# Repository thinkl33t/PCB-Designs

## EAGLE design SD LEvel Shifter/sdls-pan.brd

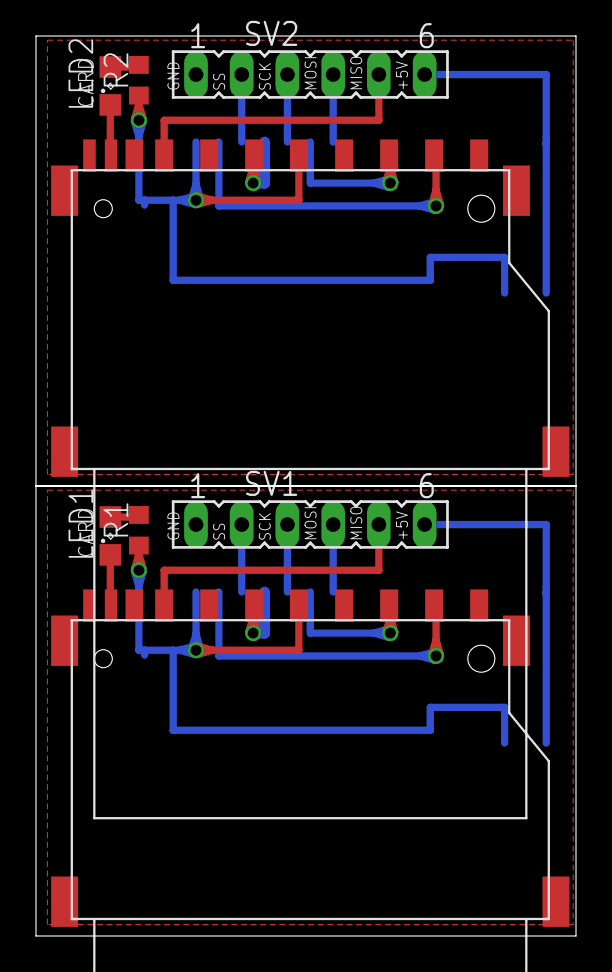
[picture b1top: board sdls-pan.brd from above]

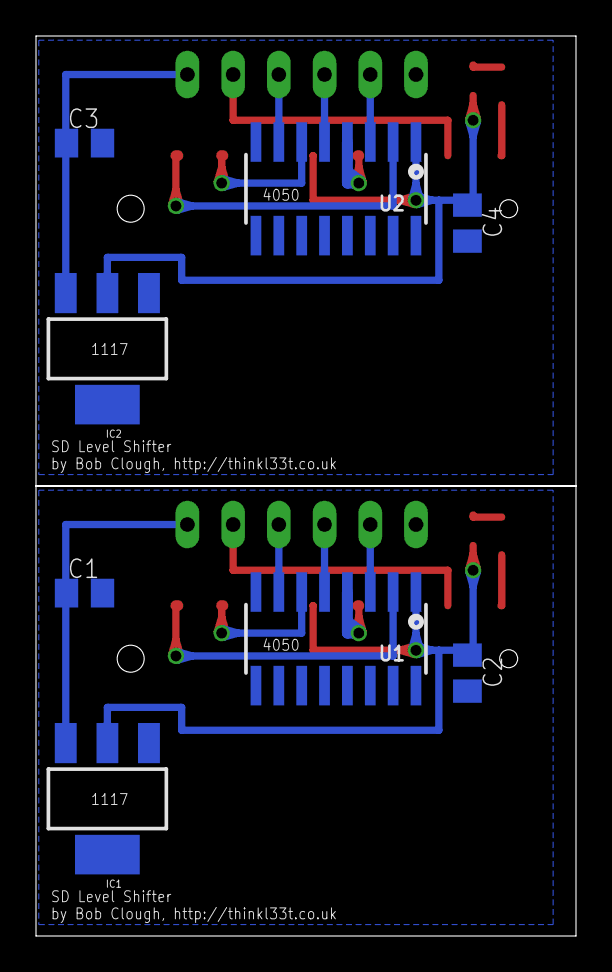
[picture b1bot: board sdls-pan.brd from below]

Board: 2 copper layers, 30.0 x 50.0 mm, 16 parts (8 on the bottom side), 24 nets.

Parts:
C1, C2, C3, C4: C0805K
IC1, IC2: SOT223
LED1, LED2: SML0805
R1, R2: R0603
SV1, SV2: FE06
U1, U2: SOIC16
U$1, U$2: SD_CARD; MEM1055

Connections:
+3V1: C4.1, IC2.2, R2.1, U2.1, U$2.P4
+3V3: C2.1, IC1.2, R1.1, U1.1, U$1.P4
+5V: C1.1, IC1.3, SV1.6
+5V1: C3.1, IC2.3, SV2.6
GND: C1.2, C2.2, IC1.1, SV1.1, U1.8, U$1.P3, U$1.P6, U$1.SHIELD0, U$1.SHIELD1, U$1.SHIELD2, U$1.SHIELD3, U$1.WP
GND1: C3.2, C4.2, IC2.1, SV2.1, U2.8, U$2.P3, U$2.P6, U$2.SHIELD0, U$2.SHIELD1, U$2.SHIELD2, U$2.SHIELD3, U$2.WP
MISO: SV1.5, U$1.P7
MISO1: SV2.5, U$2.P7
MOSI: SV1.4, U1.7
MOSI1: SV2.4, U2.7
unnamed: LED1.C, U$1.CD
unnamed: LED1.A, R1.2
unnamed: LED2.C, U$2.CD
unnamed: LED2.A, R2.2
SCK: SV1.3, U1.5
SCK1: SV2.3, U2.5
SS: SV1.2, U1.3
SS1: SV2.2, U2.3
S_MOSI: U1.6, U$1.P2
S_MOSI1: U2.6, U$2.P2
S_SCK: U1.4, U$1.P5
S_SCK1: U2.4, U$2.P5
S_SS: U1.2, U$1.P1
S_SS1: U2.2, U$2.P1

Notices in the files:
parts and their libraries:
SparkFun: Licensing: CC v3.0 Share-Alike You are welcome to use this library for commercial purposes.
microbuilder: This work is placed in the public domain, and may be freely used for commercial and non-commercial work with the following conditions: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
